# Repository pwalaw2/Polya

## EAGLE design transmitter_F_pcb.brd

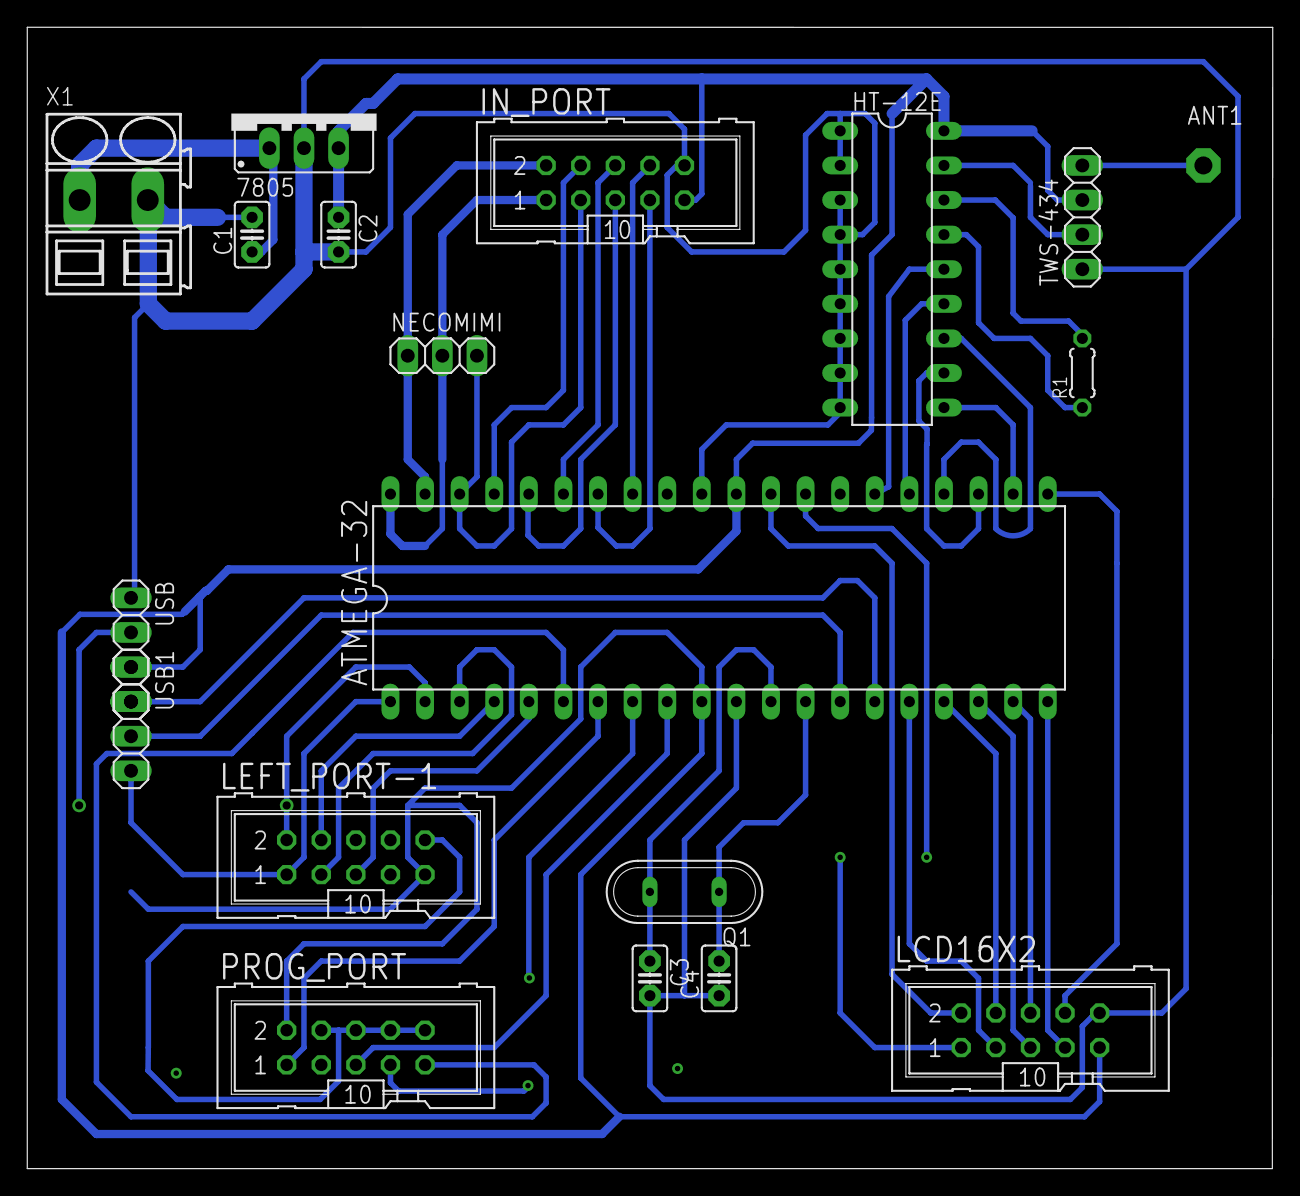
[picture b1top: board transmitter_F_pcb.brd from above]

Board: 2 copper layers, 91.5 x 83.8 mm, 19 parts (0 on the bottom side), 43 nets.

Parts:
7805: 78XXS
ANT1: PAD-01
ATMEGA-32: DIL40
C1: 0.33uF; C2.5-2
C2: 0.1uF; C2.5-2
C3, C4: 22pF; C2.5-2
HT-12E: DIL18
IN_PORT: ML10
LCD16X2: ML10
LEFT_PORT-1: ML10
NECOMIMI: 1X03
PROG_PORT: ML10
Q1: QS
R1: 750k; 0204/5
TWS-434: 1X04
USB, USB1: 1X04
X1: SMKDSP_1,5/2

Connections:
GND1: 7805.GND, ATMEGA-32.11, ATMEGA-32.31, C1.2, C2.2, C3.2, C4.1, HT-12E.1, HT-12E.2, HT-12E.3, HT-12E.4, HT-12E.5, HT-12E.6, HT-12E.7, HT-12E.8, HT-12E.9, IN_PORT.10, LCD16X2.10, LEFT_PORT-1.10, PROG_PORT.4, PROG_PORT.6, PROG_PORT.8, PROG_PORT.10, TWS-434.1, USB.1, X1.2
unnamed: ATMEGA-32.27, LEFT_PORT-1.6
unnamed: ATMEGA-32.29, LCD16X2.2
unnamed: 7805.IN, C1.1, X1.1
unnamed: ATMEGA-32.40, IN_PORT.1
unnamed: ATMEGA-32.28, LCD16X2.1
unnamed: ATMEGA-32.39, IN_PORT.2
unnamed: ATMEGA-32.6, PROG_PORT.9
unnamed: HT-12E.15, R1.1
unnamed: HT-12E.16, R1.2
unnamed: ATMEGA-32.12, C3.1, Q1.2
unnamed: ATMEGA-32.13, C4.2, Q1.1
unnamed: ATMEGA-32.38, IN_PORT.3, NECOMIMI.3
unnamed: ATMEGA-32.37, IN_PORT.4
unnamed: ATMEGA-32.36, IN_PORT.5
unnamed: ATMEGA-32.35, IN_PORT.6
unnamed: ATMEGA-32.34, IN_PORT.7
unnamed: ATMEGA-32.33, IN_PORT.8
unnamed: ATMEGA-32.8, PROG_PORT.7
unnamed: ATMEGA-32.9, PROG_PORT.5
unnamed: ATMEGA-32.7, PROG_PORT.1
unnamed: ATMEGA-32.22, HT-12E.10
unnamed: ATMEGA-32.23, HT-12E.11
unnamed: ATMEGA-32.24, HT-12E.12
unnamed: ATMEGA-32.25, HT-12E.13
unnamed: ATMEGA-32.26, HT-12E.14
unnamed: HT-12E.17, TWS-434.2
unnamed: ATMEGA-32.32, LEFT_PORT-1.7
unnamed: ANT1.1, TWS-434.4
unnamed: ATMEGA-32.16, LCD16X2.3
unnamed: ATMEGA-32.17, LCD16X2.4
unnamed: ATMEGA-32.18, LCD16X2.5
unnamed: ATMEGA-32.19, LCD16X2.6
unnamed: ATMEGA-32.20, LCD16X2.7
unnamed: ATMEGA-32.21, LCD16X2.8
unnamed: ATMEGA-32.1, LEFT_PORT-1.1, USB1.4
unnamed: ATMEGA-32.2, LEFT_PORT-1.2, USB.2
unnamed: ATMEGA-32.3, LEFT_PORT-1.3
unnamed: ATMEGA-32.4, LEFT_PORT-1.4
unnamed: ATMEGA-32.5, LEFT_PORT-1.5
S$45: ATMEGA-32.14, USB1.3
S$46: ATMEGA-32.15, USB.4
VCC: 7805.OUT, ATMEGA-32.10, ATMEGA-32.30, C2.1, HT-12E.18, IN_PORT.9, LCD16X2.9, LEFT_PORT-1.9, PROG_PORT.2, TWS-434.3, USB.3

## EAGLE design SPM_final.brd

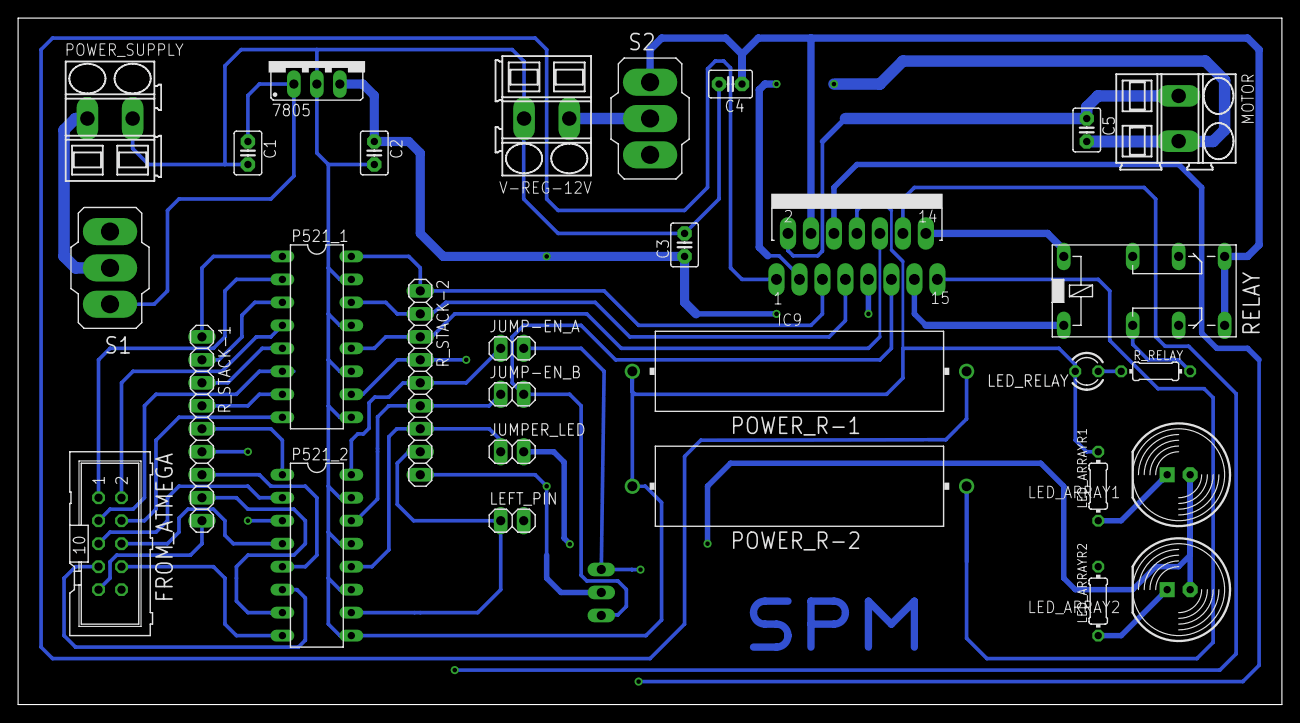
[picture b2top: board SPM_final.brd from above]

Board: 2 copper layers, 139.7 x 75.9 mm, 31 parts (1 on the bottom side), 44 nets.

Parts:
7805: 78XXS
C1: 0.33uF; C2.5-3
C2: 0.1uF; C2.5-3
C3, C4: 100nF; C2.5-3
C5: C2.5-3
FROM_ATMEGA: ML10
IC9: L298; MULTIWATT-15
JUMP-EN_A: 1X02
JUMP-EN_B: 1X02
JUMPER_LED: 1X02
LED_ARRAY1, LED_ARRAY2: LED10MM
LED_ARRAYR1, LED_ARRAYR2: 330; 0204/7
LED_RELAY: LED3MM
LEFT_PIN: 1X02
MAIN_JUMPERS: 1X03
MOTOR: SMKDSP_1,5/2
P521_1, P521_2: DIL16
POWER_R-1, POWER_R-2: HPS932
POWER_SUPPLY: SMKDSP_1,5/2
RELAY: 351
R_RELAY: 330; 0204/7
R_STACK-1, R_STACK-2: 1X09
S1, S2: 320-916
V-REG-12V: SMKDSP_1,5/2

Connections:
GND1: 7805.GND, C1.2, C2.2, C3.2, C4.2, IC9.8, LED_ARRAYR1.2, LED_ARRAYR2.2, LED_RELAY.K, P521_1.9, P521_1.11, P521_1.13, P521_1.15, P521_2.9, P521_2.11, P521_2.13, P521_2.15, POWER_R-1.2, POWER_R-2.2, POWER_SUPPLY.2, V-REG-12V.2
unnamed: FROM_ATMEGA.1, P521_1.2
unnamed: FROM_ATMEGA.2, P521_1.4
unnamed: FROM_ATMEGA.3, P521_1.6
unnamed: FROM_ATMEGA.4, P521_1.8
unnamed: FROM_ATMEGA.5, P521_2.2
unnamed: FROM_ATMEGA.6, P521_2.4
unnamed: FROM_ATMEGA.7, P521_2.6
unnamed: FROM_ATMEGA.8, P521_2.8
unnamed: FROM_ATMEGA.9, R_STACK-1.9
unnamed: P521_1.1, R_STACK-1.1
unnamed: P521_1.3, R_STACK-1.2
unnamed: P521_1.5, R_STACK-1.3
unnamed: P521_1.7, R_STACK-1.4
unnamed: P521_2.1, R_STACK-1.5
unnamed: P521_2.3, R_STACK-1.6
unnamed: P521_2.5, R_STACK-1.7
unnamed: P521_2.7, R_STACK-1.8
unnamed: C4.1, IC9.4, RELAY.S1, RELAY.S2, S2.1
unnamed: JUMPER_LED.2, LED_ARRAY1.A, LED_ARRAY2.A
unnamed: IC9.5, P521_1.16, R_STACK-2.1
unnamed: IC9.7, P521_1.14, R_STACK-2.2
unnamed: IC9.10, P521_1.12, R_STACK-2.3
unnamed: IC9.12, P521_1.10, R_STACK-2.4
unnamed: JUMP-EN_A.1, P521_2.16, R_STACK-2.5
unnamed: JUMP-EN_B.1, P521_2.14, R_STACK-2.6
unnamed: JUMPER_LED.1, P521_2.12, R_STACK-2.7
unnamed: LEFT_PIN.1, P521_2.10, R_STACK-2.8
unnamed: C5.1, IC9.2, MOTOR.1
unnamed: C5.2, IC9.3, MOTOR.2
unnamed: IC9.13, RELAY.1
unnamed: IC9.11, JUMP-EN_B.2, MAIN_JUMPERS.3
unnamed: IC9.6, JUMP-EN_A.2, MAIN_JUMPERS.1
unnamed: IC9.14, RELAY.16
unnamed: LED_ARRAY1.K, LED_ARRAYR1.1
unnamed: IC9.1, POWER_R-1.1
unnamed: IC9.15, POWER_R-2.1
unnamed: 7805.IN, C1.1, S1.1
unnamed: LED_RELAY.A, R_RELAY.1
unnamed: RELAY.P1, R_RELAY.2
unnamed: POWER_SUPPLY.1, S1.2
unnamed: S2.2, V-REG-12V.1
unnamed: LED_ARRAY2.K, LED_ARRAYR2.1
VCC: 7805.OUT, C2.1, C3.1, IC9.9, MAIN_JUMPERS.2, R_STACK-2.9

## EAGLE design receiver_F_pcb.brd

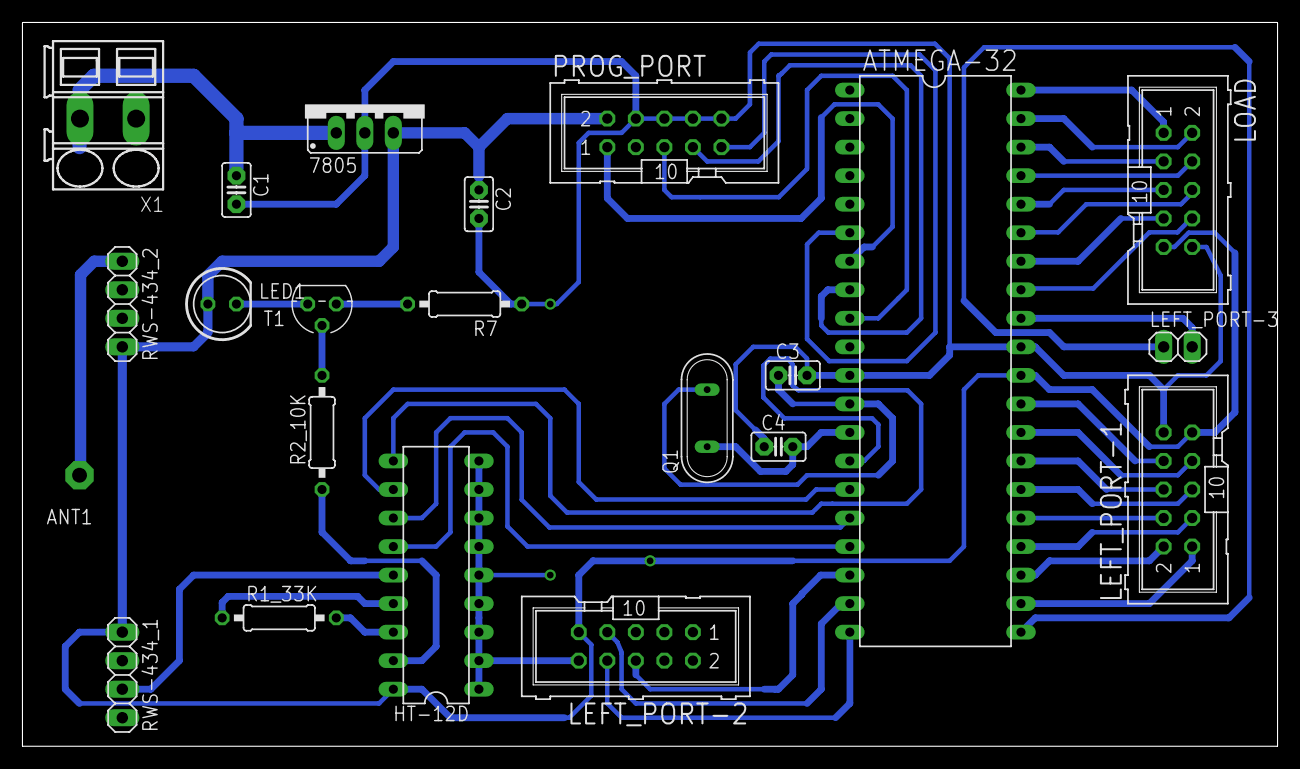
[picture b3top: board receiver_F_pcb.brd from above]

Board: 2 copper layers, 111.7 x 64.4 mm, 22 parts (0 on the bottom side), 47 nets.

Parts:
7805: 78XXS
ANT1: PAD-01
ATMEGA-32: DIL40
C1: 0.33uF; C2.5-2
C2: 0.1uF; C2.5-2
C3, C4: 22pF; C2.5-2
HT-12D: DIL18
LED1: LED5MM
LEFT_PORT-1, LEFT_PORT-2: ML10
LEFT_PORT-3: 1X02
LOAD: ML10
PROG_PORT: ML10
Q1: QS
R1_33K, R2_10K: 0207/10
R7: 470; 0207/10
RWS-434_1, RWS-434_2: 1X04
T1: 2N3904; TO92
X1: SMKDSP_1,5/2

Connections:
GND1: 7805.GND, ATMEGA-32.11, ATMEGA-32.31, C1.2, C2.2, C3.2, C4.1, HT-12D.1, HT-12D.2, HT-12D.3, HT-12D.4, HT-12D.5, HT-12D.6, HT-12D.7, HT-12D.8, HT-12D.9, LEFT_PORT-1.10, LEFT_PORT-2.10, LOAD.10, PROG_PORT.4, PROG_PORT.6, PROG_PORT.8, PROG_PORT.10, R7.1, RWS-434_1.4, RWS-434_2.2, RWS-434_2.3, X1.1
unnamed: HT-12D.17, R2_10K.1
unnamed: R2_10K.2, T1.2
unnamed: 7805.IN, C1.1, X1.2
unnamed: R7.2, T1.3
unnamed: ANT1.1, RWS-434_2.1
unnamed: LED1.K, T1.1
unnamed: HT-12D.14, RWS-434_1.3
unnamed: HT-12D.15, R1_33K.1
unnamed: HT-12D.16, R1_33K.2
unnamed: ATMEGA-32.12, C3.1, Q1.2
unnamed: ATMEGA-32.13, C4.2, Q1.1
unnamed: ATMEGA-32.22, LEFT_PORT-1.1
unnamed: ATMEGA-32.23, LEFT_PORT-1.2
unnamed: ATMEGA-32.9, PROG_PORT.5
unnamed: ATMEGA-32.24, LEFT_PORT-1.3
unnamed: ATMEGA-32.6, PROG_PORT.9
unnamed: ATMEGA-32.8, PROG_PORT.7
unnamed: ATMEGA-32.7, PROG_PORT.1
unnamed: ATMEGA-32.14, HT-12D.10
unnamed: ATMEGA-32.15, HT-12D.11
unnamed: ATMEGA-32.16, HT-12D.12
unnamed: ATMEGA-32.17, HT-12D.13
unnamed: ATMEGA-32.25, LEFT_PORT-1.4
unnamed: ATMEGA-32.40, LOAD.1
unnamed: ATMEGA-32.39, LOAD.2
unnamed: ATMEGA-32.38, LOAD.3
unnamed: ATMEGA-32.37, LOAD.4
unnamed: ATMEGA-32.36, LOAD.5
unnamed: ATMEGA-32.35, LOAD.6
unnamed: ATMEGA-32.34, LOAD.7
unnamed: ATMEGA-32.33, LOAD.8
unnamed: ATMEGA-32.26, LEFT_PORT-1.5
unnamed: ATMEGA-32.27, LEFT_PORT-1.6
unnamed: ATMEGA-32.28, LEFT_PORT-1.7
unnamed: ATMEGA-32.29, LEFT_PORT-1.8
unnamed: ATMEGA-32.21, LEFT_PORT-3.1
unnamed: ATMEGA-32.32, LEFT_PORT-3.2
unnamed: ATMEGA-32.1, LEFT_PORT-2.1
unnamed: ATMEGA-32.2, LEFT_PORT-2.2
unnamed: ATMEGA-32.3, LEFT_PORT-2.3
unnamed: ATMEGA-32.4, LEFT_PORT-2.4
unnamed: ATMEGA-32.5, LEFT_PORT-2.5
unnamed: ATMEGA-32.18, LEFT_PORT-2.6
unnamed: ATMEGA-32.19, LEFT_PORT-2.7
unnamed: ATMEGA-32.20, LEFT_PORT-2.8
VCC: 7805.OUT, ATMEGA-32.10, ATMEGA-32.30, C2.1, HT-12D.18, LED1.A, LEFT_PORT-1.9, LEFT_PORT-2.9, LOAD.9, PROG_PORT.2, RWS-434_1.1, RWS-434_2.4

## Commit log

2017-03-20 Online Banking_v01.war
2017-03-20 Online_Banking_v03.sql
2017-03-20 Brain_Controlled_SPM_PCB_Schematics_v07.sch
2017-03-20 Brain_Controlled_SPM_PCB_Layouts.brd
2017-03-20 Full Autonomous Driving Car_v01.prj
